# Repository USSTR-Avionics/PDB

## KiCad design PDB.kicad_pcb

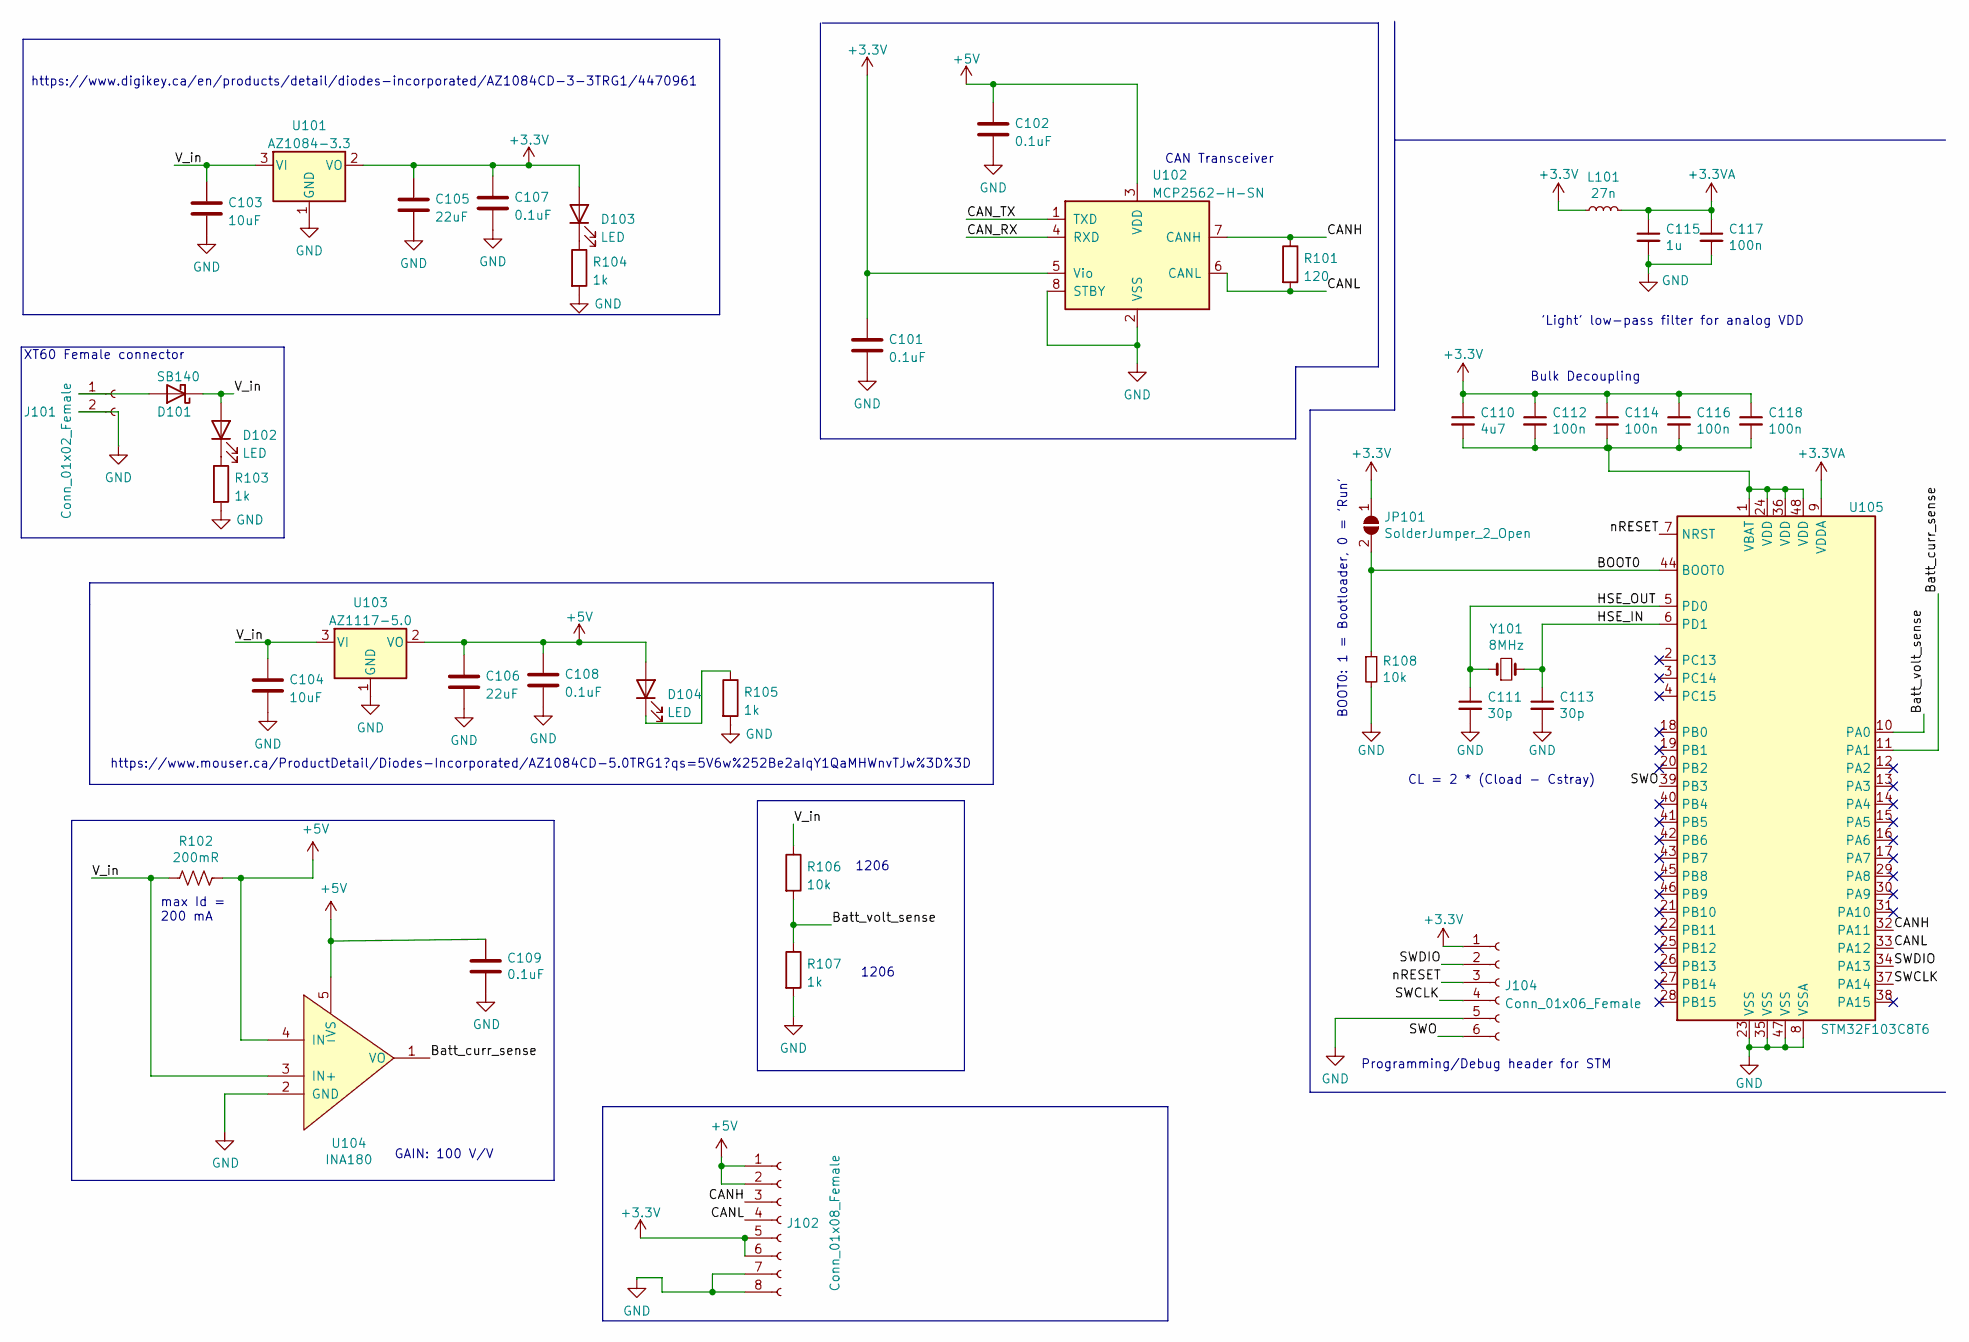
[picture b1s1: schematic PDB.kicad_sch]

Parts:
C101, C102, C107, C108, C109: 0.1uF; C_0805_2012Metric_Pad1.18x1.45mm_HandSolder
C103, C104: 10uF; C_0805_2012Metric_Pad1.18x1.45mm_HandSolder
C105, C106: 22uF; C_0805_2012Metric_Pad1.18x1.45mm_HandSolder
C110: 4u7; C_0805_2012Metric_Pad1.18x1.45mm_HandSolder; LCSC Part # C19666
C111, C113: 30p; C_0805_2012Metric_Pad1.18x1.45mm_HandSolder; LCSC Part # C1570
C112, C114, C116, C117, C118: 100n; C_0805_2012Metric_Pad1.18x1.45mm_HandSolder; LCSC Part # C1525
C115: 1u; C_0805_2012Metric_Pad1.18x1.45mm_HandSolder; LCSC Part # C52923
D101: SB140; D_DO-41_SOD81_P10.16mm_Horizontal
D102, D103, D104: LED; LED_0805_2012Metric_Pad1.15x1.40mm_HandSolder
J101: Conn_01x02_Female; AMASS_XT60PW-F_1x02_P7.20mm_Horizontal
J102: Conn_01x08_Female; PinHeader_1x08_P1.27mm_Horizontal
J104: Conn_01x06_Female; Tag-Connect_TC2030-IDC-FP_2x03_P1.27mm_Vertical
JP101: SolderJumper_2_Open; SolderJumper-2_P1.3mm_Open_Pad1.0x1.5mm
L101: 27n; L_0402_1005Metric; LCSC Part # C18830
R101: 120; R_0805_2012Metric_Pad1.20x1.40mm_HandSolder
R102: 200mR; R_0805_2012Metric_Pad1.20x1.40mm_HandSolder
R103, R104, R105: 1k; R_0805_2012Metric_Pad1.20x1.40mm_HandSolder
R106: 10k; R_1206_3216Metric_Pad1.30x1.75mm_HandSolder
R107: 1k; R_1206_3216Metric_Pad1.30x1.75mm_HandSolder
R108: 10k; R_0805_2012Metric_Pad1.20x1.40mm_HandSolder; LCSC Part # C25744
U101: AZ1084-3.3; TO-252-2
U102: MCP2562-H-SN; SOIC-8_3.9x4.9mm_P1.27mm
U103: AZ1117-5.0; TO-252-3_TabPin2
U104: INA180; SOT-23-5_HandSoldering
U105: STM32F103C8T6; LQFP-48_7x7mm_P0.5mm; LCSC Part # C8734
Y101: 8MHz; Crystal_SMD_5032-2Pin_5.0x3.2mm; LCSC Part # C115962

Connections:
+3.3V: C101.1, C105.1, C107.1, C110.1, C112.1, C114.1, C116.1, C118.1, D103.2 (A), J102.5, J102.6, J104.1, JP101.1 (A), L101.1, U101.2 (VO), U102.5 (Vio)
+3.3VA: C115.1, C117.1, L101.2, U105.9 (VDDA)
+5V: C102.1, C106.1, C108.1, C109.1, D104.2 (A), J102.1, J102.2, R102.1, U102.3 (VDD), U103.2 (VO), U104.4 (IN-), U104.5 (VS)
/BOOT0: JP101.2 (B), R108.1, U105.44 (BOOT0)
/Batt_curr_sense: U104.1 (VO), U105.11 (PA1)
/Batt_volt_sense: R106.2, R107.1, U105.10 (PA0)
/CANH: J102.3, R101.1, U102.7 (CANH), U105.32 (PA11)
/CANL: J102.4, R101.2, U102.6 (CANL), U105.33 (PA12)
/CAN_RX: U102.4 (RXD)
/CAN_TX: U102.1 (TXD)
/HSE_IN: C113.1, U105.6 (PD1), Y101.2
/HSE_OUT: C111.1, U105.5 (PD0), Y101.1
/SWCLK: J104.4, U105.37 (PA14)
/SWDIO: J104.2, U105.34 (PA13)
/SWO: J104.6, U105.39 (PB3)
/V_in: C103.1, C104.1, D101.1 (K), D102.2 (A), R102.2, R106.1, U101.3 (VI), U103.3 (VI), U104.3 (IN+)
/nRESET: J104.3, U105.7 (NRST)
GND: C101.2, C102.2, C103.2, C104.2, C105.2, C106.2, C107.2, C108.2, C109.2, C111.2, C113.2, C115.2, C117.2, J101.2, J102.7, J102.8, J104.5, R103.2, R104.2, R105.2, R107.2, R108.2, U101.1 (GND), U102.2 (VSS), U102.8 (STBY), U103.1 (GND), U104.2 (GND), U105.8 (VSSA), U105.23 (VSS), U105.35 (VSS), U105.47 (VSS)
unnamed: C110.2, C112.2, C114.2, C116.2, C118.2, U105.1 (VBAT), U105.24 (VDD), U105.36 (VDD), U105.48 (VDD)
unnamed: D101.2 (A), J101.1
unnamed: D102.1 (K), R103.1
unnamed: D103.1 (K), R104.1
unnamed: D104.1 (K), R105.1

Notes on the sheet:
BOOT0: 1 = Bootloader, 0 = 'Run'
https://www.mouser.ca/ProductDetail/Diodes-Incorporated/AZ1084CD-5.0TRG1?qs=5V6w%252Be2aIqY1QaMHWnvTJw%3D%3D
CL = 2 * (Cload - Cstray)
'Light' low-pass filter for analog VDD
Bulk Decoupling
https://www.digikey.ca/en/products/detail/diodes-incorporated/AZ1084CD-3-3TRG1/4470961
GAIN: 100 V/V
max Id = 200 mA
XT60 Female connector
CAN Transceiver
Programming/Debug header for STM
1206

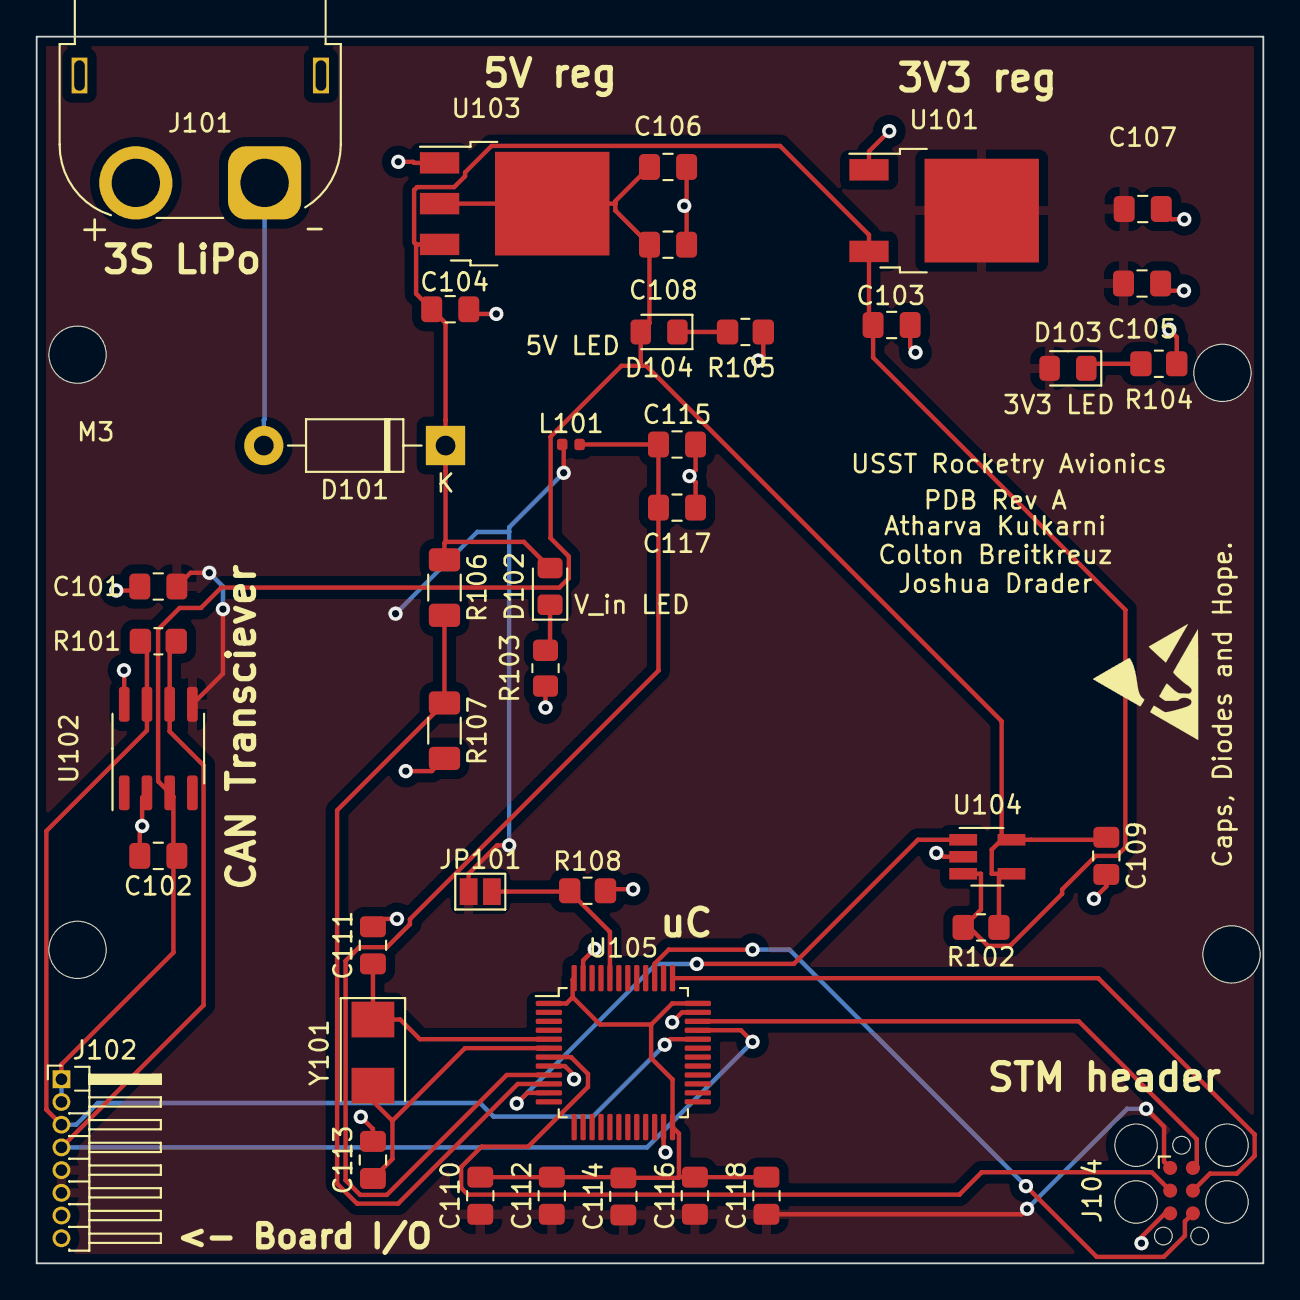
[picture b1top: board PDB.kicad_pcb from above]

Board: 2 copper layers, 68.6 x 68.6 mm, 42 parts (0 on the bottom side), 21 nets.

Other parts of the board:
M3: MountingHole_3.2mm_M3

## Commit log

2023-02-12 Add files via upload
    REV A sch capture
2023-02-12 placed componets for routing
2023-02-12 rev A PCB route and silkscreen
2023-02-12 more silkscreen fun
2023-02-12 push for production rev A
2023-03-04 changed voltage divider values for voltage measurement
2023-03-04 added BOM
